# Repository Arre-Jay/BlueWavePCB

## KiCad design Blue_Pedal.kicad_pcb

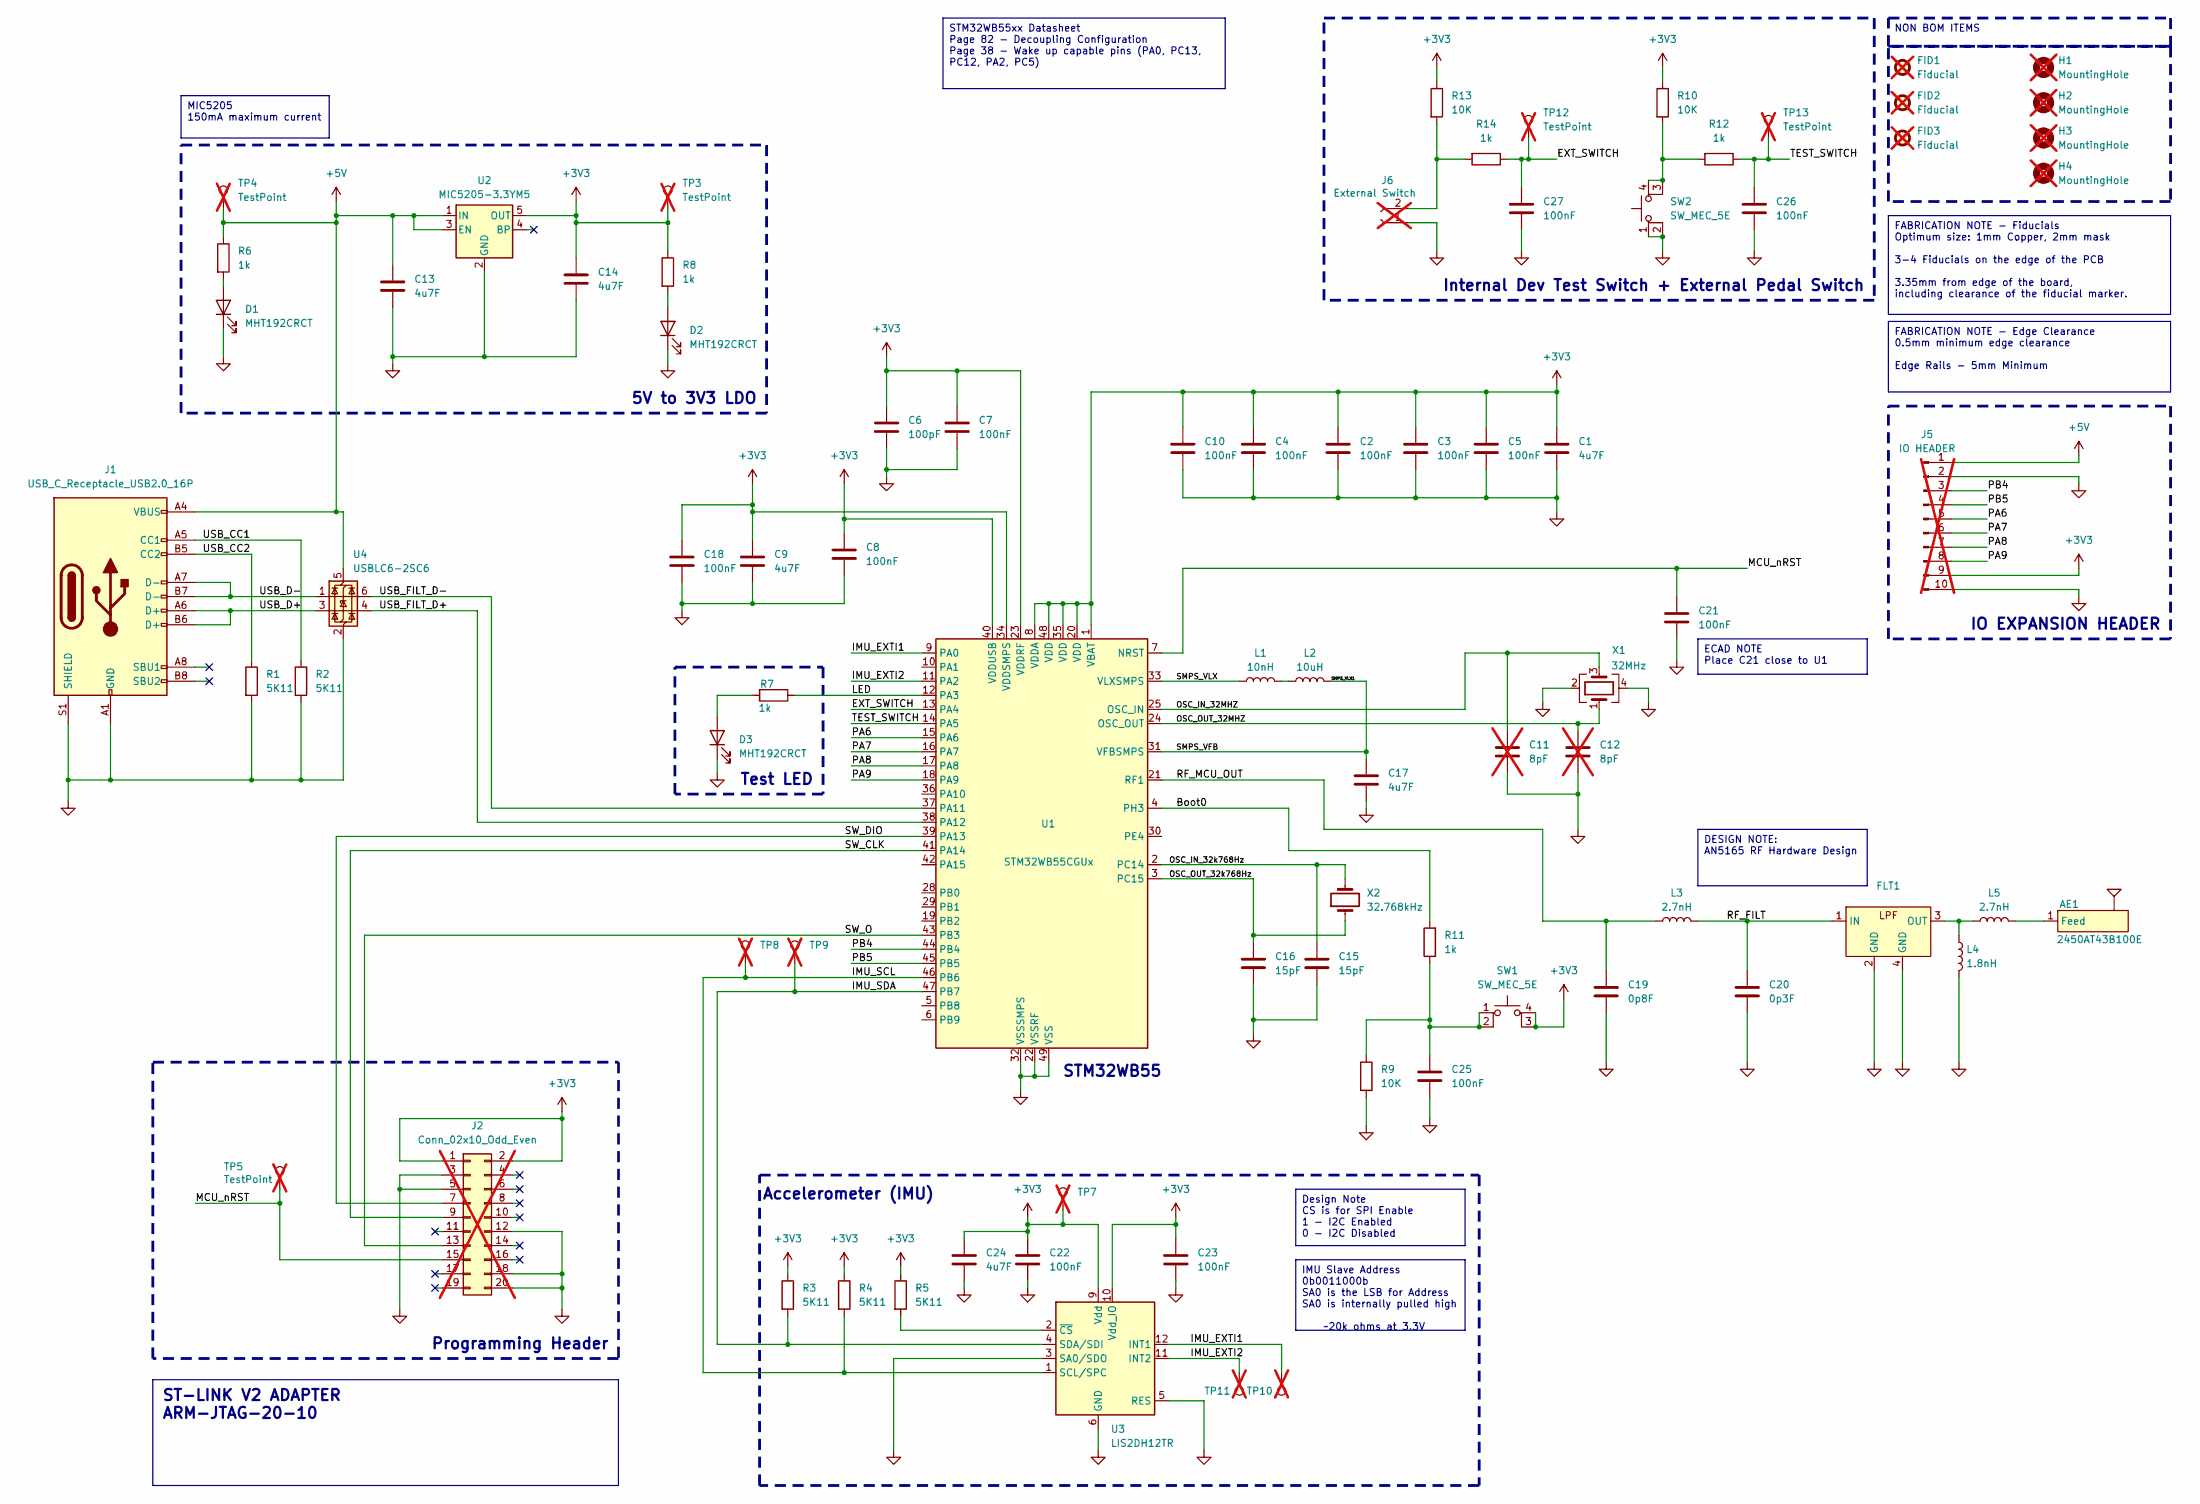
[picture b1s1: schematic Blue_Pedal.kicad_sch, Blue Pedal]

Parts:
AE1: 2450AT43B100E
C1, C9, C13, C14, C17, C24: 4u7F; C_0603_1608Metric; Manufacturer Part Number C1608X5R1V475KT000E; JLCPCB Part # C329940
C2, C3, C4, C5, C7, C8, C10, C18, C21, C22, C23, C25, C26, C27: 100nF; C_0402_1005Metric; Manufacturer Part Number C1005X7R1E104KT000F; JLCPCB Part # C189396
C6: 100pF; C_0402_1005Metric; Manufacturer Part Number CC0402KRX7R9BB101; JLCPCB Part # C281751
C11, C12: 8pF; C_0402_1005Metric; Manufacturer Part Number CGA2B2C0G1H080DT0Y0F; JLCPCB Part # C342939; not fitted
C15, C16: 15pF; C_0402_1005Metric; Manufacturer Part Number CC0402JRNPO9BN150; JLCPCB Part # C106997
C19: 0p8F; C_0402_1005Metric; Manufacturer Part Number GRM1555C1HR80BA01D; JLCPCB Part # C76988
C20: 0p3F; C_0402_1005Metric; Manufacturer Part Number GRM1555C1HR30BA01D; JLCPCB Part # C88939
D1, D2, D3: MHT192CRCT; LED_0603_1608Metric; Manufacturer Part Number MHT192CRCT; JLCPCB Part # C389517
FID1, FID2, FID3: Fiducial; Fiducial_1mm_Mask2mm; not fitted
FLT1: DLF162500LT-5028A1; Manufacturer Part Number DLF162500LT-5028A1; JLCPCB Part # C531364
H1, H2, H3, H4: MountingHole; MountingHole_3.2mm_M3; not fitted
J1: USB_C_Receptacle_USB2.0_16P; USB_C_Receptacle_GCT_USB4105-xx-A_16P_TopMnt_Horizontal; Manufacturer Part Number GT-USB-7047C; JLCPCB Part # C963218
J2: Conn_02x10_Odd_Even; EDGE_HEADER_20_WAY; not fitted
J5: IO HEADER; PinHeader_1x10_P2.54mm_Vertical; not fitted
J6: External Switch; PinHeader_1x02_P2.54mm_Vertical; not fitted
L1: 10nH; L_0402_1005Metric; Manufacturer Part Number LQG15WZ10NJ02D; JLCPCB Part # C3911026
L2: 10uH; L_0805_2012Metric; Manufacturer Part Number LQM21FN100M70L; JLCPCB Part # C98030
L3: 2.7nH; L_0402_1005Metric; Manufacturer Part Number LQG15HS2N7S02D; JLCPCB Part # C77108
L4: 1.8nH; L_0402_1005Metric
L5: 2.7nH; L_0402_1005Metric
R1, R2, R3, R4, R5: 5K11; R_0402_1005Metric; Manufacturer Part Number RC0402FR-075K11L; JLCPCB Part # C274895
R6, R7, R8, R11, R12, R14: 1k; R_0402_1005Metric; Manufacturer Part Number RC0402FR-131KL; JLCPCB Part # C4247997
R9, R10, R13: 10K; R_0402_1005Metric; Manufacturer Part Number RC0402FR-0710KL; JLCPCB Part # C60490
SW1, SW2: SW_MEC_5E; SMG-H9; Manufacturer Part Number SMG-H9; JLCPCB Part # C7435491
TP3, TP4, TP5, TP7, TP8, TP9, TP10, TP11, TP12, TP13: TestPoint; TestPoint_Pad_D1.0mm; Manufacturer Part Number NA; JLCPCB Part # NA; not fitted
U1: STM32WB55CGUx; QFN-48-1EP_7x7mm_P0.5mm_EP5.6x5.6mm; Manufacturer Part Number STM32WB55CGU6; JLCPCB Part # C404023
U2: MIC5205-3.3YM5; SOT-23-5; Manufacturer Part Number MIC5205-3.3YM5; JLCPCB Part # C37970
U3: LIS2DH12TR; LGA-12_2x2mm_P0.5mm; Manufacturer Part Number LIS2DH12TR; JLCPCB Part # C110926
U4: USBLC6-2SC6; SOT-23-6; Manufacturer Part Number USBLC6-2SC6; JLCPCB Part # C7519
X1: 32MHz; Crystal_SMD_2016-4Pin_2.0x1.6mm; Manufacturer Part Number NX2016SA-32M-EXS00A-CS06465; JLCPCB Part # C1986260
X2: 32.768kHz; Crystal_SMD_2012-2Pin_2.0x1.2mm; Manufacturer Part Number NX2012SA-32.768KHZ-EXS00A-MU00644; JLCPCB Part # C2828558

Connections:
+3V3: C1.1, C2.1, C3.1, C4.1, C5.1, C6.1, C7.1, C8.1, C9.1, C10.1, C14.1, C18.1, C22.1, C23.1, C24.1, J2.1, J2.2, J5.9, R3.1, R4.1, R5.1, R8.1, R10.1, R13.1, SW1.3 (K), SW1.4 (A), TP3.1, TP7.1, U1.1 (VBAT), U1.8 (VDDA), U1.20 (VDD), U1.23 (VDDRF), U1.34 (VDDSMPS), U1.35 (VDD), U1.40 (VDDUSB), U1.48 (VDD), U2.5 (OUT), U3.9 (Vdd), U3.10 (Vdd_IO)
+5V: C13.1, J1.A4 (VBUS), J1.A9 (VBUS), J1.B4 (VBUS), J1.B9 (VBUS), J5.1, R6.1, TP4.1, U2.1 (IN), U2.3 (EN), U4.5 (VBUS)
/Boot0: R11.2, U1.4 (PH3)
/EXT_SWITCH: C27.1, R14.1, TP12.1, U1.13 (PA4)
/IMU_EXTI1: TP10.1, U1.9 (PA0), U3.12 (INT1)
/IMU_EXTI2: TP11.1, U1.11 (PA2), U3.11 (INT2)
/IMU_SCL: R4.2, TP8.1, U1.46 (PB6), U3.1 (SCL/SPC)
/IMU_SDA: R3.2, TP9.1, U1.47 (PB7), U3.4 (SDA/SDI)
/LED: R7.1, U1.12 (PA3)
/MCU_nRST: C21.1, J2.15, TP5.1, U1.7 (NRST)
/OSC_IN_32MHZ: C11.1, U1.25 (OSC_IN), X1.3
/OSC_IN_32k768Hz: C15.1, U1.2 (PC14), X2.2
/OSC_OUT_32MHZ: C12.1, U1.24 (OSC_OUT), X1.1
/OSC_OUT_32k768Hz: C16.1, U1.3 (PC15), X2.1
/PA6: J5.5, U1.15 (PA6)
/PA7: J5.6, U1.16 (PA7)
/PA8: J5.7, U1.17 (PA8)
/PA9: J5.8, U1.18 (PA9)
/PB4: J5.3, U1.44 (PB4)
/PB5: J5.4, U1.45 (PB5)
/RF_FILT: C20.1, FLT1.1 (IN), L3.2
/RF_MCU_OUT: C19.1, L3.1, U1.21 (RF1)
/SMPS_VFB: C17.1, L2.2, U1.31 (VFBSMPS)
/SMPS_VLX: L1.1, U1.33 (VLXSMPS)
/SW_CLK: J2.9, U1.41 (PA14)
/SW_DIO: J2.7, U1.39 (PA13)
/SW_O: J2.13, U1.43 (PB3)
/TEST_SWITCH: C26.1, R12.1, TP13.1, U1.14 (PA5)
/USB_CC1: J1.A5 (CC1), R2.1
/USB_CC2: J1.B5 (CC2), R1.1
/USB_D+: J1.A6 (D+), J1.B6 (D+), U4.3 (I/O2)
/USB_D-: J1.A7 (D-), J1.B7 (D-), U4.1 (I/O1)
/USB_FILT_D+: U1.38 (PA12), U4.4 (I/O2)
/USB_FILT_D-: U1.37 (PA11), U4.6 (I/O1)
GND: C1.2, C2.2, C3.2, C4.2, C5.2, C6.2, C7.2, C8.2, C9.2, C10.2, C11.2, C12.2, C13.2, C14.2, C15.2, C16.2, C17.2, C18.2, C19.2, C20.2, C21.2, C22.2, C23.2, C24.2, C25.2, C26.2, C27.2, D1.1 (K), D2.1 (K), D3.1 (K), FLT1.2 (GND), FLT1.4 (GND), J1.A1 (GND), J1.A12 (GND), J1.B1 (GND), J1.B12 (GND), J1.S1 (SHIELD), J2.3, J2.5, J2.12, J2.18, J2.20, J5.2, J5.10, J6.1, L4.2, R1.2, R2.2, R9.2, SW2.1, SW2.2, U1.22 (VSSRF), U1.32 (VSSSMPS), U1.49 (VSS), U2.2 (GND), U3.3 (SA0/SDO), U3.5 (RES), U3.6 (GND), U3.7 (GND), U3.8 (GND), U4.2 (GND), X1.2, X1.4
unnamed: AE1.1 (Feed), L5.2
unnamed: C25.1, R9.1, R11.1, SW1.1, SW1.2
unnamed: D1.2 (A), R6.2
unnamed: D2.2 (A), R8.2
unnamed: D3.2 (A), R7.2
unnamed: FLT1.3 (OUT), L4.1, L5.1
unnamed: J6.2, R13.2, R14.2
unnamed: L1.2, L2.1
unnamed: R10.2, R12.2, SW2.3 (K), SW2.4 (A)
unnamed: R5.2, U3.2 (~CS)

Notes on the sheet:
Internal Dev Test Switch + External Pedal Switch
IMU Slave Address 0b0011000b SA0 is the LSB for Address SA0 is internally pulled high ~20k ohms at 3.3V
DESIGN NOTE: AN5165 RF Hardware Design
Test LED
ST-LINK V2 ADAPTER ARM-JTAG-20-10
MIC5205 150mA maximum current
STM32WB55xx Datasheet Page 82 - Decoupling Configuration Page 38 - Wake up capable pins (PA0, PC13, PC12, PA2, PC5)
5V to 3V3 LDO
NON BOM ITEMS
ECAD NOTE Place C21 close to U1
FABRICATION NOTE - Fiducials Optimum size: 1mm Copper, 2mm mask 3-4 Fiducials on the edge of the PCB 3.35mm from edge of the board, including clearance of the fiducial marker.
IO EXPANSION HEADER
Programming Header
Design Note CS is for SPI Enable 1 - I2C Enabled 0 - I2C Disabled
FABRICATION NOTE - Edge Clearance 0.5mm minimum edge clearance Edge Rails - 5mm Minimum
Accelerometer (IMU)
STM32WB55

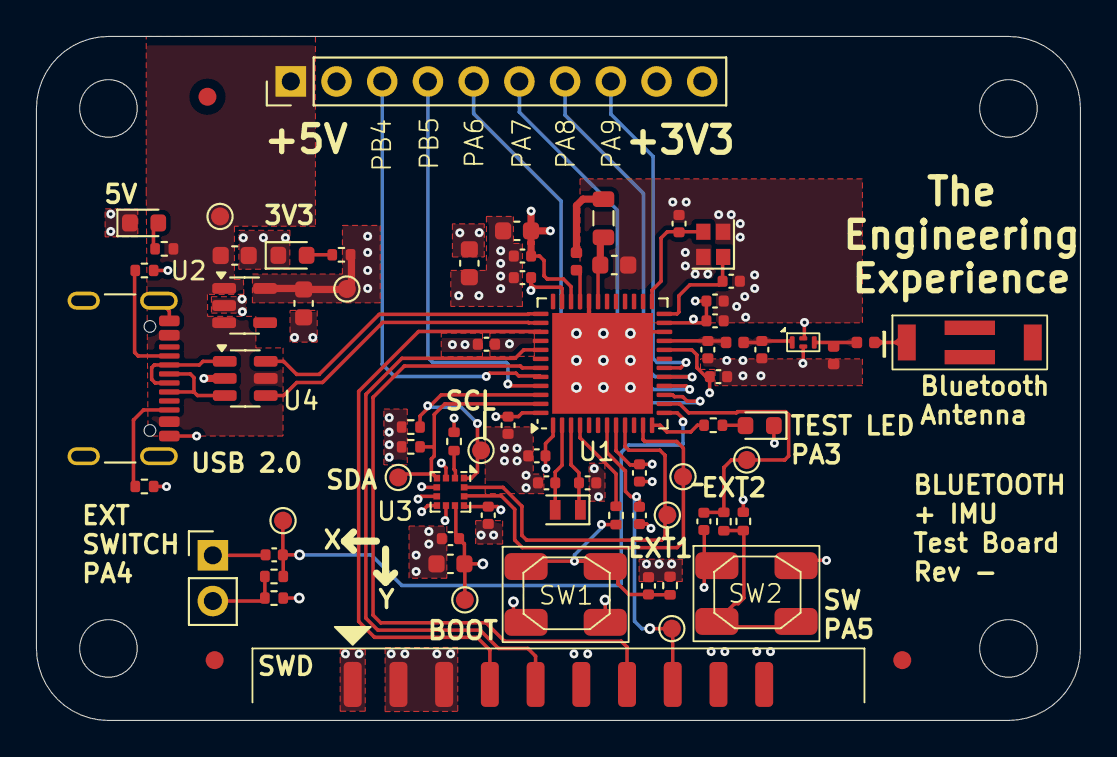
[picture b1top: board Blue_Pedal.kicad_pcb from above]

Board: 4 copper layers, 58.0 x 38.0 mm, 80 parts (0 on the bottom side), 45 nets.

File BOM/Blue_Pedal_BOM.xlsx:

Comment | Designator | Footprint | JLCPCB Part # | Description
STM32WB55CGU6 | U1 | UFQFPN-48(7x7) | C404023 | RF Microcontrollers - MCU Ultra-low-power
MIC5205-3.3YM5 | U2 | SOT-23-5 | C37970 | LDO 3V3 Voltage Regulators 150mA 1% Low
LIS2DH12TR | U3 | LGA-12(2x2) | C110926 | Accelerometers MEMS digital output motion sensor
USBLC6-2SC6 | U4 | SOT-23-6 | C7519 | ESD Suppressors / TVS Diodes ESD Protection Low Cap
MHT192CRCT | D1,D2,D3 | 0603 | C389517 | 5mA Colorless transparent lens Red
USB Connector
DLF162500LT-5028A1 | FLT1 | SMD-4P,0.8x1.6mm | C531364 | Low pass 0.33dB SMD-4P,0.8x1.6mm RF Filters
2450AT43B100E | AE1 | - | C2917721 | 1.3dBi Chip Antenna 2.4GHz 2W
NX2012SA-32.768KHZ-EXS00A-MU00644 | X2 | 2012-2P | C2828558 | Crystal 32.768kHz
NX2016SA-32M-EXS00A-CS06465 | X1 | 2016-4P | C1986260 | Crystal 32MHz
7914G-1-000E | SW1, SW2 | - | C840653 | Round Button 100mA
LQG15HS10NJ02D | L1 | 0402 | C77103 | 500mA 10nH ±5% 260mΩ 0402 Inductors (SMD) ROHS
LQM21FN100M70L | L2 | 0805 | C98030 | FIXED IND 10UH 100MA 780MOHM SMD
LQG15HS2N7S02D | L3, L5 | 0402 | C77108 | 800mA 2.7nH 120mΩ 0402 Inductors (SMD)
LQG15HS1N8S02D | L4 | 0402 | C77107 | 1.8nH 0402 Inductors (SMD) ROHS
RC0402FR-075K11L | R1,R2,R3,R4,R5 | 0402 | C274895 | 62.5mW Thick Film Resistors 50V ±100ppm/℃ ±1% 5.11kΩ 0402 Chip Resisto
RC0402FR-131KL | R6,R7,R8,R11,R12,R14 | 0402 | C4247997 | 62.5mW Thick Film Resistors ±100ppm/℃ ±1% 1kΩ 0402 Chip Resistor
RC0402FR-0710KL | R9,R10,R13 | 0402 | C60490 | 62.5mW Thick Film Resistors 50V ±100ppm/℃ ±1% 10kΩ 0402 Chip Resistor
C1608X5R1V475KT000E | C1,C9,C13,C14,C17,C24 | 0603 | C329940 | 35V 4.7uF X5R ±10% 0603 MLCC
C1005X7R1E104KT000F | C2,C3,C4,C5,C7,C8,C10,C18,C21,C22,C23,C25,C26,C27 | 0402 | C189396 | 25V 100nF X7R ±10% 0402 Multilayer Ceramic Capacitors MLCC
CC0402KRX7R9BB101 | C6 | 0402 | C281751 | 50V 100pF X7R ±10% 0402 MLCC
CC0402JRNPO9BN150 | C15, C16 | 0402 | C106997 | 50V 15pF NP0 ±5% 0402 Multilayer Ceramic Capacitors MLCC
GJM1555C1HR80BB01D | C19 | 0402 | C76915 | 50V 0.8pF 0402 Multilayer Ceramic Capacitors MLCC
CQ0402ARNPO9BNR30 | C20 | 0402 | C1870422 | 50V 0.3pF 0402 Multilayer Ceramic Capacitors MLCC

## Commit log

2024-07-24 Added files
